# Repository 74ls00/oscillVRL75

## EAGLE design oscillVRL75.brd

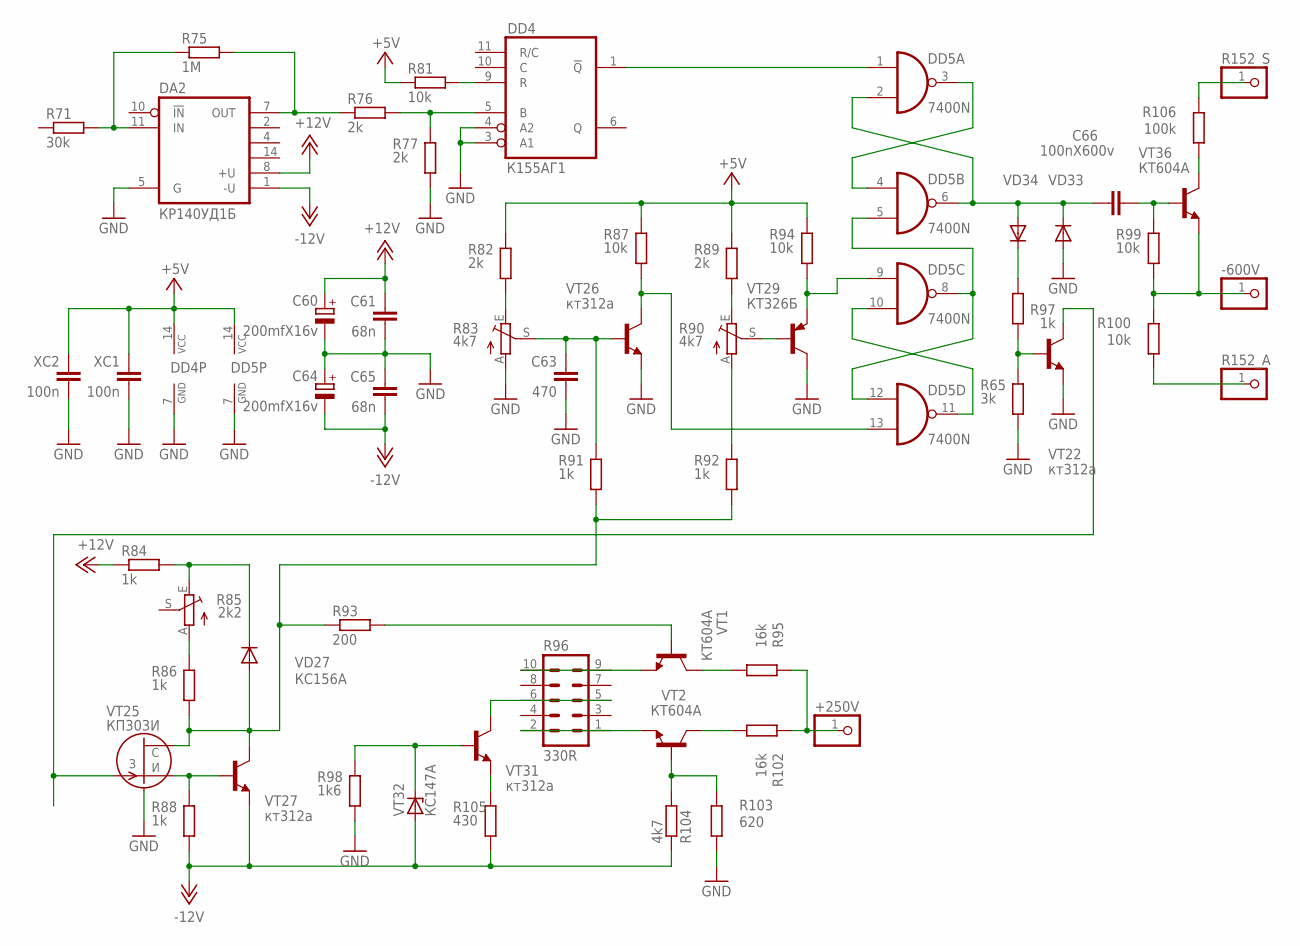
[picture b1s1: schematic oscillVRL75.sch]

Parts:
+250V: PINHD-1X1; 1X01
-600V: PINHD-1X1; 1X01
C60, C64: 200mfX16v; E2,5-6
C61, C65: 68n; C0805
C63: 470; C025-025X050
C66: 100nX600v; C050-025X075
DA2: КР140УД1Б; DIL14
DD4: К155АГ1; DIL14
DD5: 7400N; DIL14
R65: 3k; M0805
R71: 30k; M0805
R75: 1M; M0805
R76, R77, R82, R89: 2k; M0805
R81, R87, R94: 10k; M0805
R83, R90: 4k7; S64Y
R84, R86, R88, R91, R92, R97: 1k; M0805
R85: 2k2; S64Y
R93: 200; M0805
R95, R102: 16k; M1206
R96: 330R; MA05-2
R98: 1k6; M0805
R99, R100: 10k; M1206
R103: 620; M1206
R104: 4k7; M1206
R105: 430; M0805
R106: 100k; M1206
R152_A, R152_S: PINHD-1X1; 1X01
VD27: КС156А; SOD80C
VD33, VD34: DIODE-SOD80C; SOD80C
VT1, VT2, VT36: КТ604А; TO126V
VT22, VT26, VT27, VT31: кт312а; TO92-ECB
VT25: КП303И; TO72
VT29: КТ326Б; TO18
VT32: КС147А; DO35Z10
XC1, XC2: 100n; C0805

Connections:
+5V: DD4.14 (VCC), DD5.14 (VCC), R81.1, R82.2, R87.2, R89.2, R94.2, XC1.1, XC2.1
+12V: C60.+, C61.1, DA2.8 (+U), R84.1
-12V: C64.-, C65.2, DA2.1 (-U), R88.1, R104.1, R105.1, VT27.E, VT32.A
GND: C60.-, C61.2, C63.2, C64.+, C65.1, DA2.5 (G), DD4.3 (A1), DD4.4 (A2), DD4.7 (GND), DD5.7 (GND), R65.1, R77.1, R83.A, R98.1, R103.1, VD33.A, VT22.E, VT25.4 (GND), VT26.E, VT29.3 (C), XC1.2, XC2.2
unnamed: DA2.11 (IN), R71.2, R75.1
unnamed: DA2.7 (OUT), R75.2, R76.1
unnamed: R82.1, R83.E
unnamed: DD4.9 (R), R81.2
unnamed: DD4.1 (!Q), DD5.1 (I0)
unnamed: DD4.5 (B), R76.2, R77.2
unnamed: C66.1, DD5.2 (I1), DD5.6 (O), VD33.C, VD34.A
unnamed: C63.1, R83.S, R91.2, VT26.B
unnamed: DD5.3 (O), DD5.4 (I0)
unnamed: DD5.10 (I1), DD5.11 (O)
unnamed: DD5.13 (I1), R87.1, VT26.C
unnamed: R89.1, R90.E
unnamed: DD5.5 (I1), DD5.8 (O), DD5.12 (I0)
unnamed: R90.A, R92.2
unnamed: R90.S, VT29.2 (B)
unnamed: R97.2, VD34.C
unnamed: DD5.9 (I0), R94.1, VT29.1 (E)
unnamed: C66.2, R99.2, VT36.3 (B)
unnamed: -600V.1, R99.1, R100.2, VT36.1 (E)
unnamed: R100.1, R152_A.1
unnamed: R106.2, R152_S.1
unnamed: R106.1, VT36.2 (C)
unnamed: R65.2, R97.1, VT22.B
unnamed: VT22.C, VT25.3 (G)
unnamed: R88.2, VT25.1 (S), VT27.B
unnamed: R93.2, VT1.3 (B)
unnamed: R85.A, R86.2
unnamed: R84.2, R85.E, VD27.C
unnamed: R86.1, R91.1, R92.1, R93.1, VD27.A, VT25.2 (D), VT27.C
unnamed: R96.9, R96.10, VT1.1 (E)
unnamed: R96.5, R96.6, VT31.C
unnamed: R96.1, R96.2, VT2.1 (E)
unnamed: R95.1, VT1.2 (C)
unnamed: R102.1, VT2.2 (C)
unnamed: +250V.1, R95.2, R102.2
unnamed: R103.2, R104.2, VT2.3 (B)
unnamed: R105.2, VT31.E
unnamed: R98.2, VT31.B, VT32.C

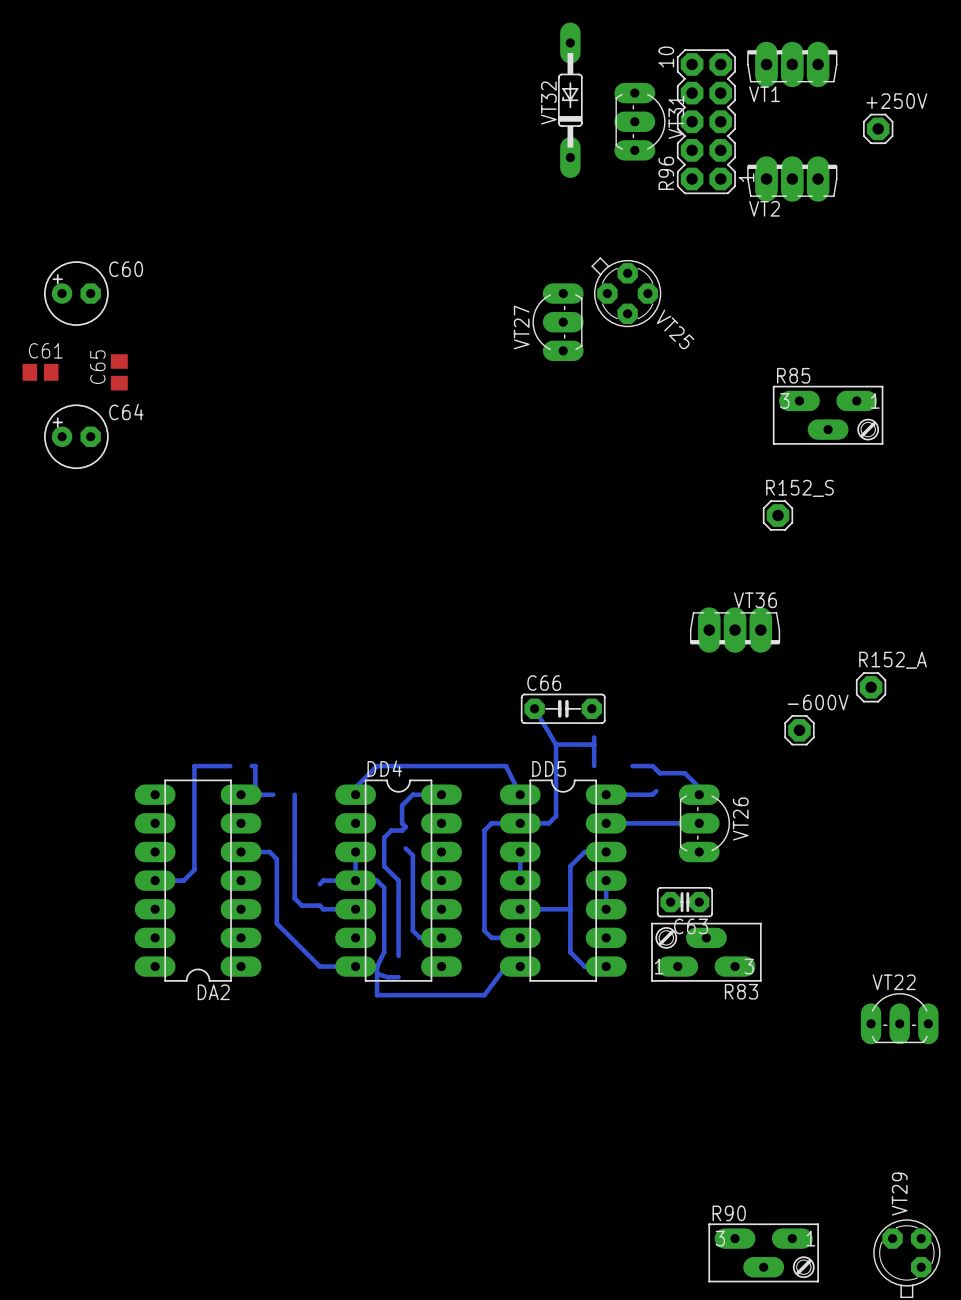
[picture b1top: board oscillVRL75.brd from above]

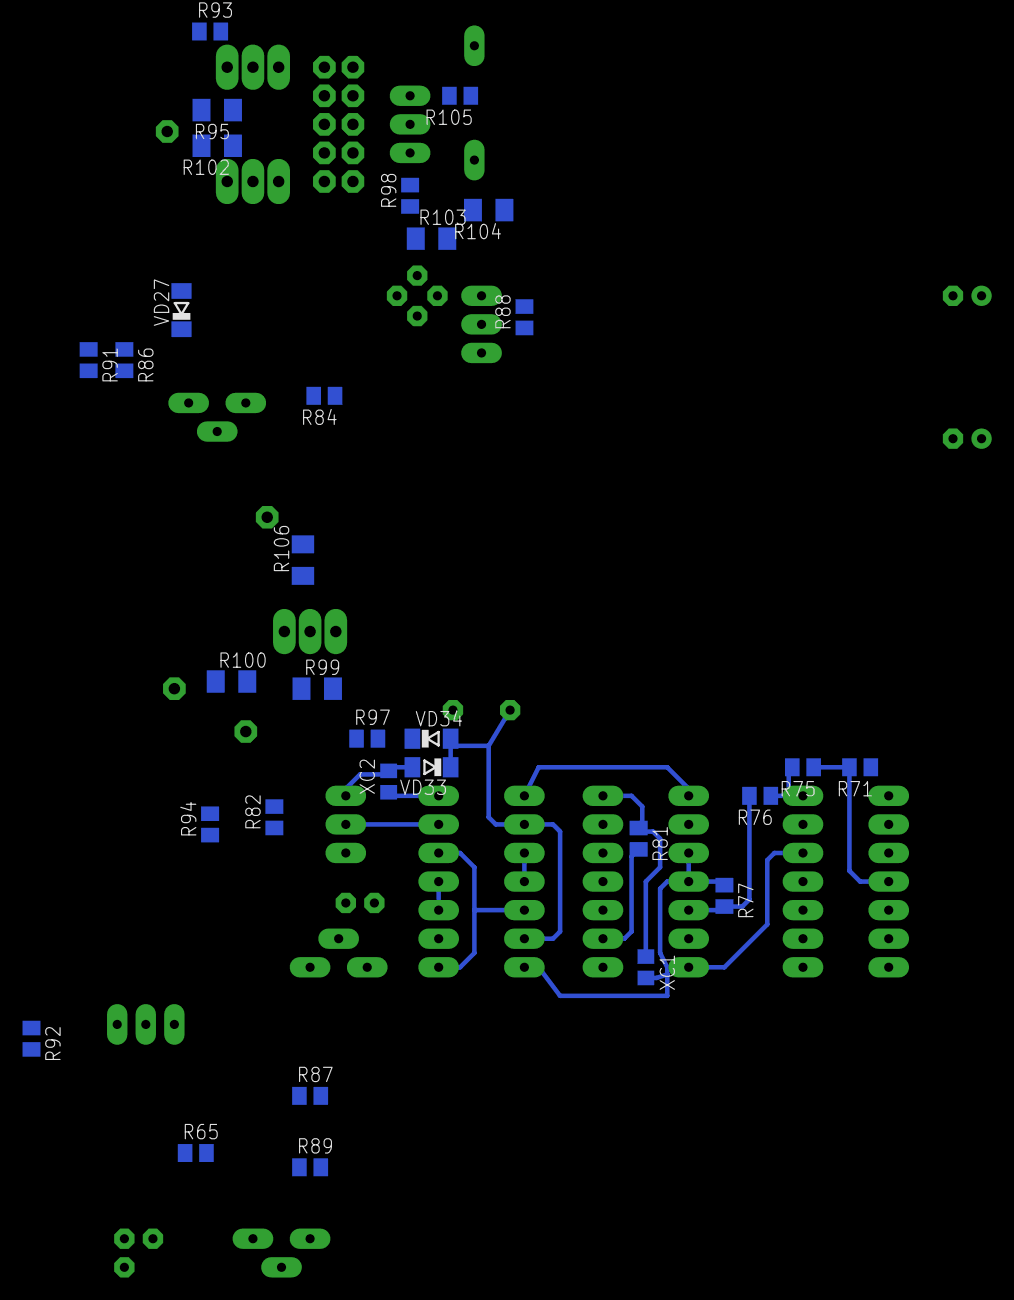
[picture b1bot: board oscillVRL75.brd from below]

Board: 2 copper layers, 58 parts (31 on the bottom side), 42 nets.
